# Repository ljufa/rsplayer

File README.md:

<p align="center">
  <picture>
    <source media="(prefers-color-scheme: dark)" srcset="docs/_assets/banner-dark.svg">
    
  </picture>
</p>

# RSPlayer

RSPlayer is an open-source music player written in Rust. Run it as a **headless server** on a NAS, home server or Raspberry Pi and control it from any browser or phone - or install the **desktop app** on your computer.

🏠 **[Website](https://rsplayer.de)** · 🎧 **[Online demo](https://demo.rsplayer.de)** · 📖 **[Documentation](https://docs.rsplayer.de/)** · ⬇️ **[Latest release](https://github.com/ljufa/rsplayer/releases/latest)**

https://github.com/user-attachments/assets/7cf6ef93-2251-4f85-a1cb-be5865a257d5

## Highlights

- Pure-Rust playback engine ([Symphonia](https://github.com/pdeljanov/Symphonia) + [cpal](https://github.com/rustaudio/cpal)) with low-latency ALSA / PipeWire output, or play straight in your browser
- FLAC, MP3, AAC, Opus, OGG Vorbis, WAV, AIFF, CAF, DSD (DSF/DFF), APE
- Cue sheets: albums ripped to a single file play as separate tracks
- Multiroom: synchronized playback across devices with automatic discovery
- Parametric EQ and DSP presets, EBU R128 loudness normalization, automatic resampling
- Internet radio and a podcast client - subscribe to shows and resume episodes where you stopped
- Optional scrobbling to ListenBrainz (or a self-hosted, compatible server) and Last.fm
- Visualizer, synchronized lyrics, sleep timer, library browsing, dynamic playlists
- Subsonic-compatible API: browse and stream your library from Subsonic apps (Symfonium, DSub, Amperfy, ...)
- SMB/NFS network share mounting, Home Assistant integration, DIY hardware control

See the [full feature list](https://docs.rsplayer.de/#/?id=features) and [feature comparison](https://docs.rsplayer.de/#/feature_parity).

## Install

**Which one do I need?**

| | Linux | macOS · Windows | Android |
|---|---|---|---|
| **Server** - runs in the background, you control it from a browser or phone. Best for a Raspberry Pi, NAS or always-on audio PC. | [Install script](#linux-server) | [Download](#macos-and-windows) | - |
| **Desktop app** - a normal app window on the computer you're using. | [Snap / Flatpak / script](#linux-desktop-app) | [Download](#macos-and-windows) | [APK](#android) |
| **Docker** | [docker run](#docker) | - | - |

### Linux server

Works on Debian, Ubuntu, Raspberry Pi OS, Fedora and Arch, on x86_64, ARM (every Raspberry Pi) and RISC-V:

```bash
bash <(curl -s https://raw.githubusercontent.com/ljufa/rsplayer/main/install.sh)
```

Then open **`http://<device-ip>`** (for example `http://raspberrypi.local`) in a browser. Updates come with your normal `apt upgrade` / `dnf upgrade`.

<details>
<summary>Prefer to add the package repository yourself?</summary>

Debian / Ubuntu / Raspberry Pi OS:

```bash
sudo curl -fsSL -o /usr/share/keyrings/rsplayer.gpg https://ljufa.github.io/rsplayer-pkg/rsplayer.gpg
echo "deb [signed-by=/usr/share/keyrings/rsplayer.gpg] https://ljufa.github.io/rsplayer-pkg/deb stable main" | sudo tee /etc/apt/sources.list.d/rsplayer.list
sudo apt update && sudo apt install rsplayer
```

Fedora / RHEL / openSUSE:

```bash
sudo curl -fsSL -o /etc/yum.repos.d/rsplayer.repo https://ljufa.github.io/rsplayer-pkg/rpm/rsplayer.repo
sudo dnf install rsplayer
```

`.deb`, `.rpm` and `.pkg.tar.zst` files for manual install are on the [release page](https://github.com/ljufa/rsplayer/releases/latest).
</details>

### Linux desktop app

#### Native .deb/.rpm package
```bash
bash <(curl -s https://raw.githubusercontent.com/ljufa/rsplayer/main/install_desktop.sh)
```

#### Snap on Ubuntu
```bash
sudo snap install rsplayer
```
#### Flatpak
```bash
flatpak install https://ljufa.github.io/rsplayer-flatpak/io.github.ljufa.rsplayer.flatpakref
```

The Snap and Flatpak are sandboxed. For bit-perfect output to USB DACs, see [sandbox permissions](https://docs.rsplayer.de/#/installation?id=desktop-app-flatpak-and-snap).

### macOS and Windows

Download from the [latest release](https://github.com/ljufa/rsplayer/releases/latest):

| | Server | Desktop app |
|---|---|---|
| **macOS** | `rsplayer_darwin_arm64` (Apple Silicon) or `rsplayer_darwin_amd64` (Intel) - `chmod +x` and run | `.dmg` |
| **Windows** | `rsplayer_windows_amd64.exe` - just run it | `rsplayer-desktop_windows_amd64.exe` |

After starting the server, open `http://localhost:8000`. On Windows, installed ASIO drivers can be selected in Settings → Audio interface. More in the [macOS](https://docs.rsplayer.de/#/installation?id=macos) and [Windows](https://docs.rsplayer.de/#/installation?id=windows) guides.

> ASIO is a trademark and software of Steinberg Media Technologies GmbH.

### Android

Download `rsplayer_<version>_android.apk` from the [latest release](https://github.com/ljufa/rsplayer/releases/latest) and open it on the phone (Android 8.0+). The full player runs inside the app: put music in the shared **Music** folder, grant the media permission on first start, and playback works offline with lock-screen controls. Details in the [Android guide](https://docs.rsplayer.de/#/installation?id=android).

With [Obtainium](https://obtainium.imranr.dev/) the app updates itself from GitHub releases: tap the badge on the phone and it picks the APK for your device.

### Docker

```bash
docker run -p 8000:80 -v ${MUSIC_DIR}:/music -v rsplayer_data:/opt/rsplayer --device /dev/snd -it --rm ljufa/rsplayer:latest
```

Then open `http://localhost:8000`.

<details>
<summary>docker compose</summary>

```yaml
services:
  rsplayer:
    image: ljufa/rsplayer:latest
    devices:
      - /dev/snd
    ports:
      - 8000:80
    volumes:
      - ${MUSIC_DIR}:/music:ro
      - 'rsplayer_volume:/opt/rsplayer'
    restart: unless-stopped
volumes:
  rsplayer_volume:
    driver: local
```
</details>

**Next steps:** [configuration](https://docs.rsplayer.de/#/configuration) · [usage guide](https://docs.rsplayer.de/#/usage) · [troubleshooting](https://docs.rsplayer.de/#/troubleshooting)

## Home Assistant & DIY hardware

Control RSPlayer from [Home Assistant](https://www.home-assistant.io/) with the [rsplayer_hacs_plugin](https://github.com/ljufa/rsplayer_hacs_plugin). For DIY builds, see [rsplayer_hardware](https://github.com/ljufa/rsplayer_hardware) and [rsplayer_firmware](https://github.com/ljufa/rsplayer_firmware).

## AI notice

RSPlayer is built by a human maintainer who uses generative AI as a development tool. The maintainer decides what gets built, reviews the results, tests every release and signs off on everything that ships.

RSPlayer itself contains no AI and makes no requests to AI services.

Bug reports and pull requests are welcome whether or not AI tools were involved in making them. Everything that gets merged is reviewed by a person.

## Contributing

Contributions are welcome - open an issue or a pull request. See [Building from source](https://docs.rsplayer.de/#/build).

## License

MIT, see [LICENSE](LICENSE).

## Disclaimer

The software is provided "as is", without warranty. Use sensible volume levels and follow your audio hardware's ratings. See the full [disclaimer](https://docs.rsplayer.de/#/disclaimer) and [privacy policy](https://rsplayer.de/privacy.html).

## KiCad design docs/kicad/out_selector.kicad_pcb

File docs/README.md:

# RSPlayer - Rust-native music server

RSPlayer is an open-source, headless music server primarily for Linux. Run it on your NAS, home server, Raspberry Pi, or any x86_64/ARM machine and control it from any browser. A native desktop app (Linux x86_64/ARM64, macOS, Windows) is also available, and on Android.

It runs as a systemd service and exposes a responsive web UI, making it a great fit for machines without a monitor or keyboard — but equally at home on a dedicated desktop audio PC. Hardware and DIY integrations (GPIO DAC control, custom firmware) are fully optional.

Under the hood RSPlayer uses [Symphonia](https://github.com/pdeljanov/Symphonia) for audio decoding and [Cpal](https://github.com/rustaudio/cpal) for output, with a Rust-native audio pipeline for low-latency, high-performance playback.

**Website → https://rsplayer.de** · **Online demo → https://demo.rsplayer.de**

## Getting Started

- [Installation](installation.md) — supported platforms, install methods, and verification
- [Configuration](configuration.md) — audio settings, volume control, and hardware integration
- [Usage Guide](usage.md) — web interface, queue, library, keyboard shortcuts
- [Troubleshooting](troubleshooting.md) — common issues and fixes

## Features

- **Low Latency Output**: Direct output to ALSA or PipeWire minimizes latency.
- **Multiroom Playback**: Native synchronized playback across multiple RSPlayer devices — automatic discovery on the LAN, encrypted QUIC streaming, millisecond-level sync, per-room volume and EQ. See [Multiroom Playback](multiroom.md).
- **Local Browser Playback**: Stream audio directly to your web browser for local playback.
- **Automatic Resampling**: High-quality FFT-based resampling (via rubato) when the output device doesn't support the source sample rate — no configuration needed. Automatically probes fallback rates for ALSA drivers that misreport their supported range.
- **Fixed Output Sample Rate**: Optionally lock the output to a specific sample rate, overriding automatic detection.
- **Multiple Music Sources**: Configure multiple local directories and network mounts as music sources, all scanned together.
- **Network Storage Management**: Discover, mount, and manage SMB/CIFS and NFS shares directly from the settings page.
- **Remote Libraries (S3)**: Play a library stored on S3-compatible storage (Amazon S3, Backblaze B2, Cloudflare R2, MinIO, Garage, or a NAS folder published with `rclone serve s3`) without mounting anything: enter its URL and access key, songs are scanned and streamed over the network. Works in the Android app too, which cannot mount network shares, so a home library is playable from anywhere. See [Remote Library](remote_library.md).
- **Subsonic API**: Browse and stream the library from third-party Subsonic apps such as Symfonium, DSub, Amperfy, play:Sub, Feishin or Supersonic. Turn it on and set a password in Settings. See [Subsonic API](subsonic.md).
- **Adjustable Playback Thread Priority**: Customize the priority of the playback thread up to a real-time rating of 99 via the settings page.
- **Dedicated CPU Core for Playback**: By default, the playback thread is pinned to a single CPU core for optimized performance.
- **Web UI Remote Control**: Manage your playback remotely with an intuitive web interface.
- **Flexible Volume Control**: Choose ALSA mixer, PipeWire, or software gain volume control, with hardware control also supported via RSPlayer firmware integration.
- **Volume Persistence**: Volume level is saved on change and restored on restart, defaulting to 0 on first use to prevent hardware-max shock.
- **Comprehensive Music Library Management**: Scan, search, and browse your music library and online radio stations with ease.
- **Podcasts**: Find shows in the Apple Podcasts directory (or Podcast Index with a free API key), or paste an RSS feed URL, then subscribe and play episodes through the regular queue. Feeds refresh in the background, playback resumes where you stopped, and episodes are marked played automatically. See [Podcasts View](usage.md?id=podcasts-view).
- **Dynamic Playlists**: Automatically create dynamic playlists for personalized listening experiences.
- **Playlists by Genre, Year**: Browse and create playlists based on genre or year.
- **Drag-and-Drop Queue Reordering**: Reorder queue items by dragging them directly in the queue view.
- **DSP Integration**: Advanced Digital Signal Processing with parametric EQ, filters, and presets.
- **Loudness Normalization**: Per-song EBU R128 loudness normalization, toggleable from the settings page. Analysis runs automatically in the background while playback is stopped and results are stored permanently.
- **Music Visualizer**: Real-time audio visualization in the web interface, with 13 visualizer styles, including an analog VU meter.
- **Synchronized Lyrics**: Real-time synchronized lyrics support via LRCLIB integration.
- **Sleep Timer**: Pause playback after 15 to 120 minutes (or any number you type) or at the end of the current track. The timer runs on the server, so it keeps going with the app closed, and every device shows the same countdown. See [Sleep Timer](usage.md?id=sleep-timer).
- **Library Statistics**: Dedicated statistics page showing song/album/artist counts, total duration, play history, top genres, albums by decade, and loudness analysis progress.
- **Web UI Themes**: Support for customizable themes and dark/light modes (10+ built-in themes).
- **Global Keyboard Shortcuts**: Full keyboard control for playback, navigation, and search (Space, arrows, M, L, Y, S, /, ?, 1-4, F/A/P/R/O/T).
- **Breadcrumb Navigation**: Clear navigation context on all library pages.
- **Skeleton Loading & Empty States**: Visual feedback during loading and helpful empty state screens.
- **Written in Rust**: Enjoy the benefits of minimal dependencies and high performance, thanks to the Rust-native implementation.
- **Extended Hardware Control**: Support for seek and power management via firmware interactions.

### Supported Formats

FLAC, MP3, AAC, OGG Vorbis, WAV, AIFF, CAF, DSD (DSF/DFF), APE (Monkey's Audio), and SACD ISO disc images.

## Known Limitations

- **DSD passthrough bypass**: DSP (parametric EQ, filters), loudness normalization, and resampling are all bypassed for DSD files (`.dsf`, `.dff`). DSD bitstreams are passed directly to the DAC without any signal processing.
- **Radio streams**: Loudness normalization is not applied to internet radio streams — it requires pre-scanned file metadata. Seeking is not supported for streams.
- **Unsupported formats**: Opus, WMA, WavPack, and TTA are not supported.
- **Local Browser Playback**: In this mode the browser's native audio engine plays files directly. DSP, loudness normalization, resampling, visualization, and DSD playback are all unavailable — format support is limited to what the browser itself can decode. Podcast resume positions are not saved in this mode.
- **Remote libraries (S3)**: APE files and SACD ISO images on remote storage are skipped, and loudness normalization does not analyse remote songs (it would download them in full). The first scan reads the beginning of every file over the network, so a large library takes a while.
- **Subsonic API**: One user, no transcoding (apps get the original files), no jukebox mode. See [Subsonic API](subsonic.md#limits).
- **Non-Linux builds**: On macOS and Windows, network share mounting, ALSA/PipeWire volume, IR remote, system poweroff/reboot, and firmware USB integration are unavailable.

## How does RSPlayer compare?

> Approximate comparison as of November 2026. Features change frequently. See [Feature Parity](feature_parity.md) for a detailed comparison against Volumio, Roon, MPD, Navidrome, Lyrion (LMS), moOde, Daphile, and piCorePlayer.

| Feature | RSPlayer | Volumio | Moode Audio | MPD |
|---|---|---|---|---|
| Language | Rust | Node.js | PHP/Bash | C |
| Playback engine | Symphonia + cpal (pure rust) | MPD (plugin-based) | MPD (plugin-based) | plugin-based (FFmpeg, libFLAC, …) |
| OS support | Linux, macOS, Windows, Android | Linux | Linux (Pi) | Linux, macOS, Windows |
| Native desktop app variant | Linux, macOS, Windows, Android | — | — | — |
| Web UI | ✓ | ✓ | ✓ | 3rd party |
| Local browser playback | ✓ | — | — | — |
| Library on S3 storage (no mount) | ✓ | No | No | No |
| Parametric EQ / DSP | ✓ built-in | plugin (FusionDSP) | ✓ (CamillaDSP) | via plugins |
| Multi-room | ✓ | paid tier | ✓ | via plugins |
| DSD playback | ✓ | ✓ | ✓ | ✓ |
| Loudness normalization | ✓ EBU R128 (built-in analysis, no tags needed) | ReplayGain (manual MPD config) | ReplayGain | ReplayGain |
| Synchronized lyrics | ✓ | plugin (beta) | — | client dependent |
| Docker | ✓ | ✓ | — | ✓ |
| RISC-V 64 | ✓ | — | — | — |
| Home Assistant integration | ✓ | ✓ | ✓ (via MPD) | ✓ |
| DIY hardware integration | optional | — | — | — |
| License | MIT | GPL | GPL | GPL |

<sub>Based on publicly available information as of November 2026; other products change often and may have added features since. Product names are trademarks of their respective owners. Spotted an error? [Open an issue](https://github.com/ljufa/rsplayer/issues) and it will be corrected.</sub>

## Home Assistant Integration

RSPlayer can be controlled from [Home Assistant](https://www.home-assistant.io/) via the [rsplayer_hacs_plugin](https://github.com/ljufa/rsplayer_hacs_plugin).

Features include media player control (play, pause, stop, next/prev, volume) and real-time sync with `rsplayer_firmware` power state.

Install via HACS by adding `https://github.com/ljufa/rsplayer_hacs_plugin` as a custom repository.

## DIY Hardware

For DIY enthusiasts, RSPlayer offers the flexibility to integrate with custom hardware components.

- **Hardware Designs**: [rsplayer_hardware](https://github.com/ljufa/rsplayer_hardware)
- **Firmware**: [rsplayer_firmware](https://github.com/ljufa/rsplayer_firmware)

See the [Configuration](configuration.md) page for hardware integration details.

## Planned Features

- **Expanded Audio Codec Support**: Compatibility with a wider range of audio codecs.
- **Intelligent Dynamic Playlists**: Advanced dynamic playlists that adapt based on user likes or playback counts.
- **Music Recommendations**: Suggest similar tracks or artists based on listening history or current playback.
- **Generate Missing Album Cover Image**: Auto-generate album art using the album name.
- **MPD protocol support**: Compatibility with MPD clients.
- **Subsonic protocol support**: Compatibility with Subsonic clients.
- **Community plugin framework**: Extensible architecture for third-party plugins.
- **Improved playlist management**: Create/modify/delete items and playlists from everywhere.
- **Scheduled music library scans**: Define an automatic library scan interval (or cron).
- **Built-in NFS, SMB and S3 clients**: Scan and play a music library straight from network shares or S3-compatible storage, without mounting them in the OS — so remote libraries also work on Android, macOS, Windows, Snap and Flatpak.
- **Problem (bug) report with diagnostics**: Report problems directly from the app.
- **Desktop App File Logging**: Rolling log files for the desktop app, so users can capture and share diagnostics without running from a terminal.
- **Homebrew Distribution**: Install and update RSPlayer on macOS through a Homebrew formula/cask.
- **Android App on Google Play**: publish the Android app (shipped as an APK since v4.9.0) to the Play Store, and add an optional kiosk mode for dedicated players.

## Contributing

Contributions are welcome — submit a pull request or open an issue on the [GitHub repository](https://github.com/ljufa/rsplayer). To build from source, see [Building from Source](build.md).

## License

RSPlayer is licensed under the MIT license. See the [LICENSE](https://github.com/ljufa/rsplayer/blob/master/LICENSE) file for more information. See also the [Disclaimer](disclaimer.md) and [Privacy Policy](https://rsplayer.de/privacy.html).

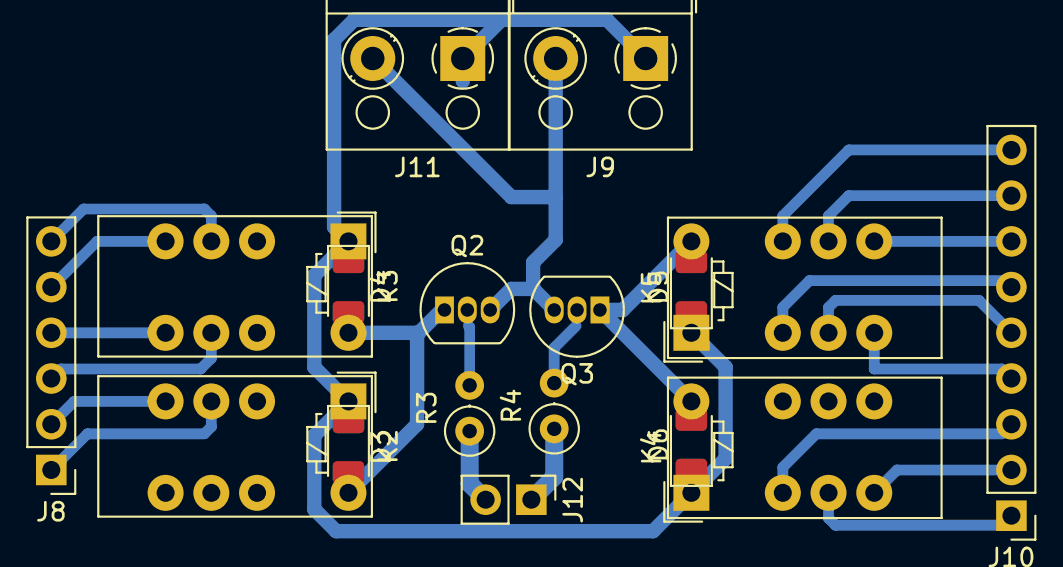
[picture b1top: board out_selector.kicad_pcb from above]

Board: 2 copper layers, 17 parts (0 on the bottom side), 23 nets.

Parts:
D3, D4, D5, D6: 1N4004; D_1206_3216Metric
J8: Mute_dac; PinHeader_1x06_P2.54mm_Vertical
J9: PWR_From_Control_Brd; TerminalBlock_RND_205-00001_1x02_P5.00mm_Horizontal
J10: Audio_Out; PinHeader_1x09_P2.54mm_Vertical
J11: PWR_To_Display_BLK; TerminalBlock_RND_205-00001_1x02_P5.00mm_Horizontal
J12: Drive_GPIO; PinHeader_1x02_P2.54mm_Vertical
K2, K3, K4, K5: G6S-2; Relay_DPDT_Omron_G6S-2
Q2, Q3: BC547; TO-92_Inline
R3, R4: 1K; R_Axial_DIN0207_L6.3mm_D2.5mm_P2.54mm_Vertical

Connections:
+5V: D3.1, D4.1, D5.1, D6.1, J9.1, J11.1, K2.1, K3.1, K4.1, K5.1
/AGND_in: J10.1, K4.4
/AGND_out_phn: J10.2, K4.5
/AGND_out_spk: J10.3, K4.3
/AL_in: J10.8, K5.9
/AL_out_phn: J10.7, K5.8
/AL_out_spk: J10.9, K5.10
/AR_in: J10.5, K5.4
/AR_out_pnh: J10.4, K5.5
/AR_out_spk: J10.6, K5.3
/GND_in: J8.1, K2.4
/GND_out: J8.2, K2.5
/GPIO9: J12.1, R4.1
/L_in: J8.6, K3.4
/L_out: J8.5, K3.5
/R_in: J8.3, K3.9
/R_out: J8.4, K3.8
/WaveIO_L8: J12.2, R3.1
GND: J9.2, J11.2, Q2.3, Q3.3
unnamed: D3.2, D4.2, K2.12, K3.12, Q2.1
unnamed: D5.2, D6.2, K4.12, K5.12, Q3.1
unnamed: Q2.2, R3.2
unnamed: Q3.2, R4.2

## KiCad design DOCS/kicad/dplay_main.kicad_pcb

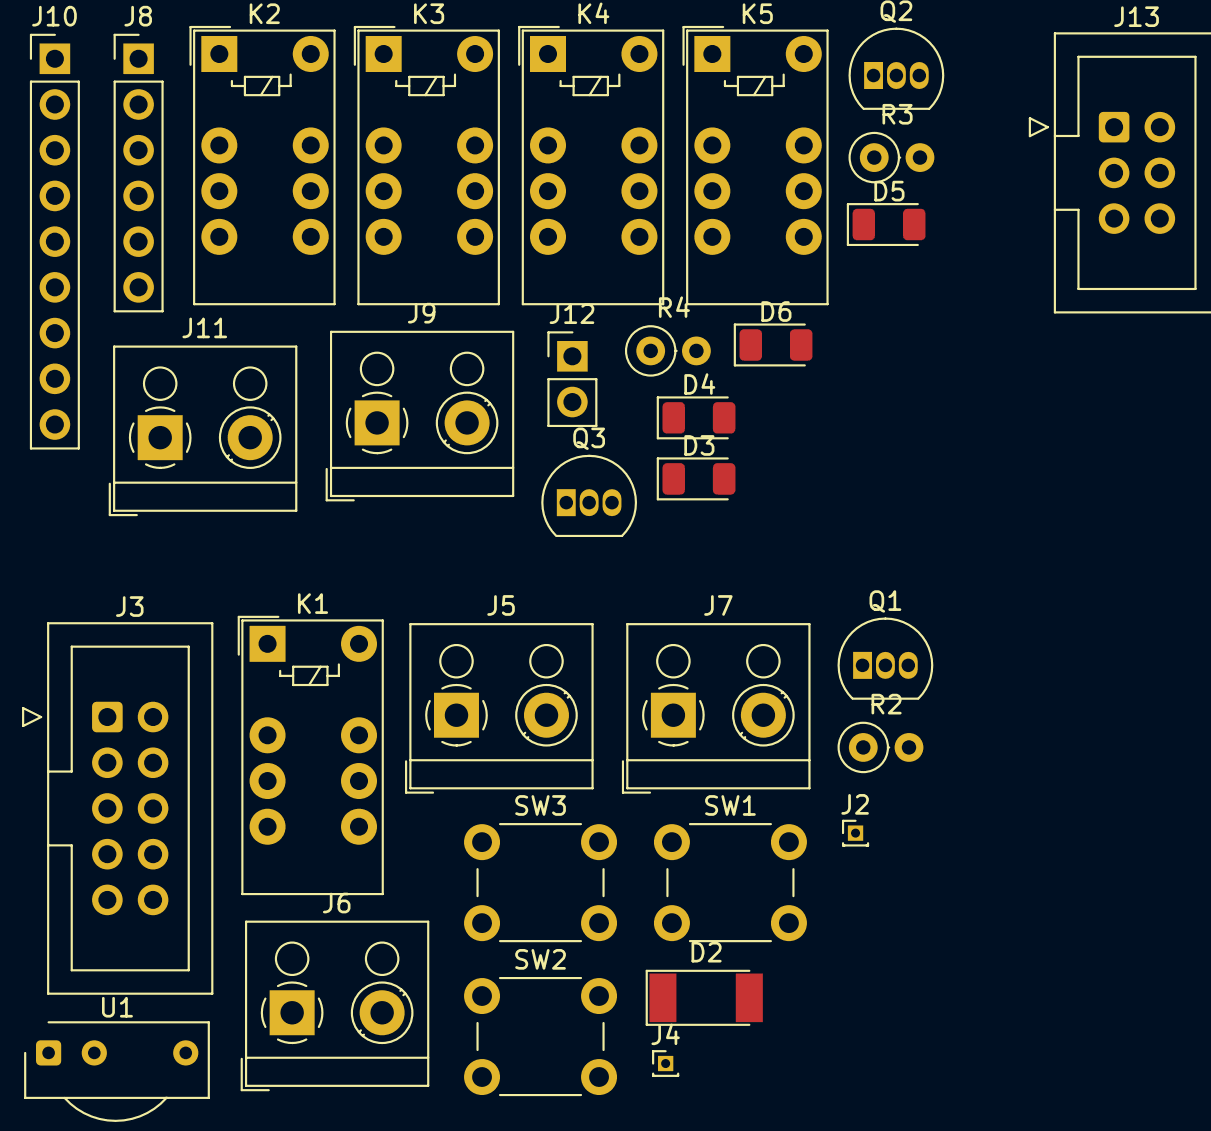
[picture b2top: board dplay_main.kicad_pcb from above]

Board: 2 copper layers, 32 parts (0 on the bottom side), 19 nets, no tracks yet.

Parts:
D2: 1N4004; D_MELF
D3, D4, D5, D6: 1N4004; D_1206_3216Metric
J2: GPIO_To_Power_off_btn; PinHeader_1x01_P1.00mm_Vertical
J3: To_RPI_GPIO; IDC-Header_2x05_P2.54mm_Vertical
J4: GPIO_To_Selector_Brd; PinHeader_1x01_P1.00mm_Vertical
J5: POWER_IN; TerminalBlock_RND_205-00001_1x02_P5.00mm_Horizontal
J6: POWER_OUT; TerminalBlock_RND_205-00001_1x02_P5.00mm_Horizontal
J7: 220_IN_OUT; TerminalBlock_RND_205-00001_1x02_P5.00mm_Horizontal
J8: Mute_dac; PinHeader_1x06_P2.54mm_Vertical
J9: PWR_From_Control_Brd; TerminalBlock_RND_205-00001_1x02_P5.00mm_Horizontal
J10: Audio_Out; PinHeader_1x09_P2.54mm_Vertical
J11: PWR_To_Display_BLK; TerminalBlock_RND_205-00001_1x02_P5.00mm_Horizontal
J12: Drive_GPIO; PinHeader_1x02_P2.54mm_Vertical
J13: Female_IDC_02x03_Odd_Even; IDC-Header_2x03_P2.54mm_Vertical
K1, K2, K3, K4, K5: G6S-2; Relay_DPDT_Omron_G6S-2
Q1, Q2, Q3: BC547; TO-92_Inline
R2: 1k; R_Axial_DIN0207_L6.3mm_D2.5mm_P2.54mm_Vertical
R3, R4: 1K; R_Axial_DIN0207_L6.3mm_D2.5mm_P2.54mm_Vertical
SW1: Volume_UP; SW_PUSH_6mm
SW2: Volume_DOWN; SW_PUSH_6mm_H5mm
SW3: Select_output_spk_phn; SW_PUSH_6mm_H5mm
U1: TSOP312xx; Vishay_CAST-3Pin

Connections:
/control_board/5V_RPI: D2.1, J5.2, K1.1, U1.2
/control_board/GPIO9: J3.9, J4.1
/control_board/GPIO15: J3.2, SW2.2
/control_board/GPIO17: J3.3, SW3.2
/control_board/GPIO18: J3.4, SW1.2
/control_board/GPIO22: J2.1, J3.8
/control_board/GPIO23: J3.7, R2.2
/control_board/GPIO27: J3.6, U1.3
/out_selector_and_mute/5V_SWITCH: D3.1, D4.1, D5.1, D6.1, J9.1, J11.1, K2.1, K3.1, K4.1, K5.1
GND: J3.1, J5.1, J6.1, J9.2, J11.2, J13.2, Q1.3, Q2.3, Q3.3, SW1.1, SW2.1, SW3.1, U1.1
unnamed: D2.2, K1.12, Q1.1
unnamed: D3.2, D4.2, K2.12, K3.12, Q2.1
unnamed: D5.2, D6.2, K4.12, K5.12, Q3.1
unnamed: J6.2, K1.5
unnamed: J7.1, K1.9
unnamed: J7.2, K1.8
unnamed: Q1.2, R2.1
unnamed: Q2.2, R3.2
unnamed: Q3.2, R4.2

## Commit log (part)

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2023-03-01 refactor settings storage
2023-03-01 fix upgrade error
2023-03-04 use rust-embed, publis binary files
2023-03-04 fix upload path
2023-03-05 fix logging
2023-03-05 add warp=info
2023-03-05 fix grep
2023-03-08 fix deb packaging
2023-03-08 add enable service
2023-03-08 use cross images
2023-03-08 do not fail
2023-03-08 remove cache
2023-03-10 - tag from version - publish docker image - update readme
2023-03-10 change background color
2023-03-10 add key pref for cache
2023-03-11 improve restarts
2023-03-12 make websocket work over https
2023-03-12 version bump
2023-06-29 add armhf v6 release
2023-06-29 add arch to deb name
2023-12-05 BREAKING: - remove spotify, mpd and lms FEATURES: reorganize music lib page add exclusion list incremental lib update add multiline url support move to seed 0.10.0 fix armhf build
2023-12-05 fix tabs
2023-12-18 Refactor and simplify code BREAKING: change database structure ( requires music dir rescan, saved playlists and setting will be destroyed)
2023-12-21 cargo fmt
2024-01-09 implement files as tree view
2024-02-02 search on files,radios and artists implement play count and like song kicad 7 increase number of results clippy && fmt fix tree layout, implement radio browser tree remove db delete implement artist 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
2024-02-18 minor bug fixes
2024-02-21 remove unfavorited
2024-02-21 error handling improvements
2024-03-14 hardware rewired
2024-03-14 run systemd unit as rsplayer (non root) user
2024-03-15 allow similar names
2024-03-15 improve migration message
2024-03-20 remove redundant async
2024-03-20 fix docker
2024-05-26 bump version, clippy fix
2024-09-13 fix playback thread long await, upgrade crates v
2024-09-16 fix bounded channel send
2024-09-21 move player_service to separate file, (re)store current song progress
2024-10-11 resolve hanging thread issuse, add radio metadata
2024-10-16 improve stop command, remove retry failed logic to prevent long running playback thread
2025-10-01 major refactoring: remove hardware part out of player (to rsplayer_firmware repo)
2025-10-01 wf fix
2025-10-01 increment versions
2025-10-01 fix cd
2025-10-02 fix installation script
2025-10-04 The `Stop` command in the music player was not resetting the playback position to the beginning of the track, instead behaving identically to the `Pause` command. This commit corrects this behavior b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
    This change includes:
    - A new `reset_progress` method in `PlayerService` to encapsulate the stop and reset logic.
    - A modification to the `command_handler` to call this new method when a `Stop` command is received.
    - A new integration test that verifies the `Stop` command correctly resets the playback progress by checking the persisted state in the `sled` database.
    - Refact
2025-10-04 Fix(settings): Prevent audio device setting from being lost
    The saved audio device setting was being lost on page load due to a race
    condition in how the application settings were managed. The settings were
    read from the database on every request, which could lead to inconsistencies
    when updating the list of available audio devices.
    This commit resolves the issue by introducing an in-memory cache for the
    settings, guarded by a `RwLock` for thread-safe access. The settings are
2025-10-05 Feat: Make artist and album names clickable links
    This change makes the artist and album names on the player page clickable links.
    - The artist link navigates to the 'Artists' tab in the music library and filters by the artist's name.
    - The album link navigates to the 'Files' tab in the music library and searches for the album's name.
    To support this, the `init` functions in `music_library_artists.rs` and `music_library_files.rs` were modified to handle a `search` query parameter from the URL.
    Fix: Correctly handle URL query parameters in routing
    The routing logic in `lib.rs` was updated to correctly parse URLs with query parameters, preventing 404 errors when navigating to pages with se
2025-10-05 Fix: Preserve search results and style clickable links
    - Modified the WebSocketOpen event handlers in `music_library_artists.rs` and `music_library_files.rs` to prevent search results from being cleared on page load.
    - Added underlining to the artist and album links on the player page to make them visually distinct.
2025-10-05 fix search param parsing
2025-10-05 implement rsplayer firmware as volume control device, do not store current volume in local db but use ctrl device
2025-10-06 fix the issue with changing alsa card index
2025-10-06 clippy fixes
2025-12-15 Squashed commit of the following: add dsd support fix prev/next song time use metadata for radiostreams implement lirc remote commands fix alsa mixer indexing replace uart with usb
2025-12-15 bump version, add migration script
2026-01-15 add more playback modes
2026-01-16 add retry logic (for network streams mostly)
2026-01-16 fix(ci): make release step robust to missing artifacts
2026-01-16 fix(package): remove hardcoded binary path from deb assets
2026-02-12 improvements, vu meter for web ui
2026-02-18 implement seek, poweron/off from firmware
2026-02-20 optimize dsp filter processing
2026-02-21 add flags for dsp an d vumeter
2026-02-22 Clippy fixes, readme updates
2026-02-23 ui consistency fixes, implement ui themes
2026-02-23 improve playback queue experience
2026-02-23 update roadmap
2026-03-01 fix prio queue bug, ha integration via custom component - ws
2026-03-01 fix target
2026-03-01 dark is default theme
2026-03-02 - add synchronized lyrics - Implement "Local Browser Playback" mode to stream audio directly to the web browser. - Add PipeWire output support using `wpctl` for volume control.
2026-03-02 update docs
2026-03-04 fix queue memory/cpu/disk bloat on large dir play, fix library artist/album name grouping, fix QuerySongsByAlbum empty results; bump to v1.8.6
    - Queue 'Play Now' on directory: replace full song-DB scan with sled scan_prefix,
    batch priority-queue updates to eliminate O(N²) sled write amplification
    - Library grouping: normalize artist/album names (case, whitespace, diacritics,
    punctuation) so tag variants merge into one entry; preserve original display title
    - QuerySongsByAlbum: fall back to verbatim sled key for pre-fix databases so songs
    are returned without requiring a rescan
2026-03-04 build rpm and arch packages
2026-03-05 improve install for other distros/arch, add test_install script
2026-03-05 fix upload
2026-03-12 loudness normalization
2026-03-15 loudness normalization improvements
2026-03-17 update Troubleshooting section
2026-03-17 move build doc to gh pages
2026-03-20 add label to hw cards
2026-03-20 bump version and release notes
2026-03-21 revert dep location
2026-03-22 auto mount managed volumes at start
2026-03-22 relnotes
2026-03-26 v2.5.5: fixed output sample rate, volume persistence, DSD bundle, SMB improvements, settings page reorganization
2026-03-26 add limitations docs
2026-03-27 feat: Add APE (Monkey's Audio) support and keyboard shortcuts
    - Add support for decoding Monkey's Audio (APE) files with a custom
    decoder and demuxer.
    - Implement comprehensive global keyboard shortcuts for playback,
    navigation, and search.
    - Introduce breadcrumb navigation for improved library browsing.
    - Enhance UI with skeleton loading screens and helpful empty state
2026-03-29 Add 12 visualizer modes, first-time setup wizard, and settings improvements
2026-03-29 Improve APE playback and scanning performance
2026-04-05 version 2.7.0
2026-04-09 version 2.7.5
2026-04-21 version 2.8.0
2026-04-25 fix: prevent metadata scan crash due to fjall lock poisoning (#8)
2026-04-25 change ci/cd to work in containers
2026-04-25 fix dockerfile.ui and remove clippy from ci.yml
2026-04-25 fix task labels and lock image versions
2026-04-25 fix test run in ci.yml 2
2026-04-26 add guards for keys - issue #8
2026-04-27 fix scroll on expand
2026-04-27 fix local cross build
2026-05-01 Bump the actions group across 1 directory with 8 updates
    Bumps the actions group with 8 updates in the / directory:
    | Package | From | To |
    | --- | --- | --- |
    | [actions/checkout](https://github.com/actions/checkout) | `5` | `6` |
    | [docker/login-action](https://github.com/docker/login-action) | `3` | `4` |
    | [docker/setup-buildx-action](https://github.com/docker/setup-buildx-action) | `3` | `4` |
2026-05-01 Bump the all-dependencies group across 1 directory with 6 updates
    Bumps the all-dependencies group with 6 updates in the / directory:
    | Package | From | To |
    | --- | --- | --- |
    | [fjall](https://github.com/fjall-rs/fjall) | `3.1.2` | `3.1.4` |
    | [tokio](https://github.com/tokio-rs/tokio) | `1.51.0` | `1.52.1` |
    | [uuid](https://github.com/uuid-rs/uuid) | `1.23.0` | `1.23.1` |
2026-05-05 Bump the all-dependencies group across 1 directory with 6 updates
    Bumps the all-dependencies group with 6 updates in the / directory:
    | Package | From | To |
    | --- | --- | --- |
    | [tokio](https://github.com/tokio-rs/tokio) | `1.52.1` | `1.52.2` |
    | [axum-server](https://github.com/programatik29/axum-server) | `0.7.3` | `0.8.0` |
    | [tower-http](https://github.com/tower-rs/tower-http) | `0.6.8` | `0.6.9` |
2026-05-05 Bump the actions group across 1 directory with 8 updates (#10)
    Bumps the actions group with 8 updates in the / directory:
    | Package | From | To |
    | --- | --- | --- |
    | [actions/checkout](https://github.com/actions/checkout) | `5` | `6` |
    | [docker/login-action](https://github.com/docker/login-action) | `3` | `4` |
    | [docker/setup-buildx-action](https://github.com/docker/setup-buildx-action) | `3` | `4` |
2026-05-15 fix scanning error for large files on 32bit arch
2026-05-15 upgrade symphonia to 0.6.0
2026-05-15 3.1.0 release notes
2026-05-22 v3.5.0: add macOS targets, software volume
2026-05-22 fix ci
2026-05-29 refactor project structure
2026-05-29 fix ui path in server
2026-05-30 make release notes
2026-05-30 update documentation
2026-06-03 Bump ubuntu from 22.04 to 26.04 in /docker
    Bumps ubuntu from 22.04 to 26.04.
    ---
    updated-dependencies:
    - dependency-name: ubuntu
    dependency-version: '26.04'
    dependency-type: direct:production
2026-06-03 Bump the all-dependencies group with 3 updates
    Bumps the all-dependencies group with 3 updates: [log](https://github.com/rust-lang/log), [rubato](https://github.com/HEnquist/rubato) and [gloo-timers](https://github.com/rustwasm/gloo).
    Updates `log` from 0.4.30 to 0.4.31
    - [Release notes](https://github.com/rust-lang/log/releases)
    - [Changelog](https://github.com/rust-lang/log/blob/master/CHANGELOG.md)
    - [Commits](https://github.com/rust-lang/log/compare/0.4.30...0.4.31)
    Updates `rubato` from 2.0.0 to 3.0.0
2026-06-03 version as input param
2026-06-03 fix webui build path
2026-06-03 fix desktop build
2026-06-10 fix tauri-cli install
2026-06-18 Bump the all-dependencies group across 1 directory with 11 updates
    Bumps the all-dependencies group with 10 updates in the / directory:
    | Package | From | To |
    | --- | --- | --- |
    | [fjall](https://github.com/fjall-rs/fjall) | `3.1.4` | `3.1.5` |
    | [chrono](https://github.com/chronotope/chrono) | `0.4.44` | `0.4.45` |
    | [log](https://github.com/rust-lang/log) | `0.4.30` | `0.4.32` |
2026-06-18 fix desktop build script
2026-06-19 fix rpm matching
2026-06-23 V4.1.0 - update demo and desktop mode, introduce bind address config, hide system and firmware sections on settings page for desktop version
2026-06-23 Bump the all-dependencies group across 1 directory with 12 updates
    Bumps the all-dependencies group with 11 updates in the / directory:
    | Package | From | To |
    | --- | --- | --- |
    | [fjall](https://github.com/fjall-rs/fjall) | `3.1.4` | `3.1.5` |
    | [chrono](https://github.com/chronotope/chrono) | `0.4.44` | `0.4.45` |
    | [log](https://github.com/rust-lang/log) | `0.4.30` | `0.4.33` |
2026-06-23 fix test in ci
2026-06-30 fix cpal 0.18.0 device enum
